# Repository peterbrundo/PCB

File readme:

👋 Hi, I’m @peterbrundo, this is my public github!
👀 I’m interested in printed circuit board design and programing!
🌱 I’m currently learning how to play the accordion!
💞️ I’m looking to collaborate on electrical hardware design
📫 peter.brundage@wayne.edu
👔 linkedin.com/in/peterbrundo
😅 This is a work in progress!

Upcoming projects
➡ PCB Buisness Card USB Keyboard

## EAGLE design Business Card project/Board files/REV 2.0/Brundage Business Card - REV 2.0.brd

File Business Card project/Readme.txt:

TO DO:
Learn how to spell business
Upload code and test
Finish soldering 0201 (0603) capacitors

Project Purpose:

The purpose of the project is to create a buisness card on a printed circuit board with some keyboard functionality! With this project I've had a few key goals in mind

	1) Learn and experiment with USB 2.0 protoco (hardware and software)
	2) Design a PCB to plug directly into a USB port
	3) Develop a working PCB CAD library with associated 3d .stp files
	4) Look and serve as a buisness card (with some style!)
	5) Use 0201 (0603 metric) sized components as a soldering challenge!
	6) Polish up on some documentation skills! (github and this readme for example)

Inspiration:

The main inspiration of this project is definetley this "Stylophone buisness card" project I saw on youtube (https://mitxela.com/projects/stylocard & https://youtu.be/zHVrY_xLM3c). I had been making PCBs at work and at home, and I thought it would be an interesting side project to do in my free time.  I liked the idea because it would be easy to present a buisness card to my friends and family.  To add my own personalized spin, I decided to make it also work as a keyboard. I think there's all sorts of possible applications such as streamdecks, custom macrobased push buttons, numpads, support for non-standard ASCII charecters, or just as a clumsy keyboard alternative. One of my favorite ideas was to have a keyboard to create keybindings for a favorite game of mine, counter strike global offensive.  Each button would correspond to in game items and equipment in the buy menu.  I could even feature some artwork on the pcb to include icons from the game itself as reference. 

V-USB

With a buisness card in mind, I needed to select a microcontroller.  Traditionally I've used Arduino UNO and MEGAs (ATMEGA family) as a starting point but they don't include USB hardware. That's when I found the V-USB library and thought it was a unique way to provide USB functionality to different ATMEGA microncontrollers.  In hindsight, I could also have chosen an Arduino Leonardo or another ATMEGA with hardware usb.  

PCB design:

To make the PCB look like a buisness card, I used a 3.5 x 2.0 inch dimension as a constraint.  I wanted the USB header to fit within these dimensions at the center of the 45 degree bend at the top right corner. 
I wanted the header centered along the curve without exceeding the 3.5 x 2.0 inch dimensions.  First I created a new eagle library and created a USB-A header following the USB 2.0 specification for the required dimenions and pinouts, even including a USB logo as best I could!  With the part in hand, I brushed up my trig to create the 45 degree bend with my USB header centered at the midddle (math included on the "47 Measures layer"). 

I then copied the V-USB circuit schmeatic from the website.  I wanted to give myself a challenge so I included 0201 (0603 Metric) sized capacitors as a soldering challenege!  Those buggers are near impossible to solder with a heat gun, so it's almost a necessiaty to have a microscope on hand.  I did order a stencil and solderpaste for this, but next time I'd rather do it by hand with a soldering iron.  Perhaps i'll include a surface mount version of the ATMEGA8 for more drag soldering practice.

For my personal info, I decided to play around with the different copper and soldermask layers to create some neat effects. The email is incorrect, and I may decide to take the rest of my contact info out from the design files later, but oh well.  

I then created my own eagle components for the rest of the parts from the V-USB schematic and included 3d .step files for everything.  I think there may be a few things that i've used from other libraries, such as the GND and +5V, but it's been a long time!

more info at http://www.obdev.at/vusb/

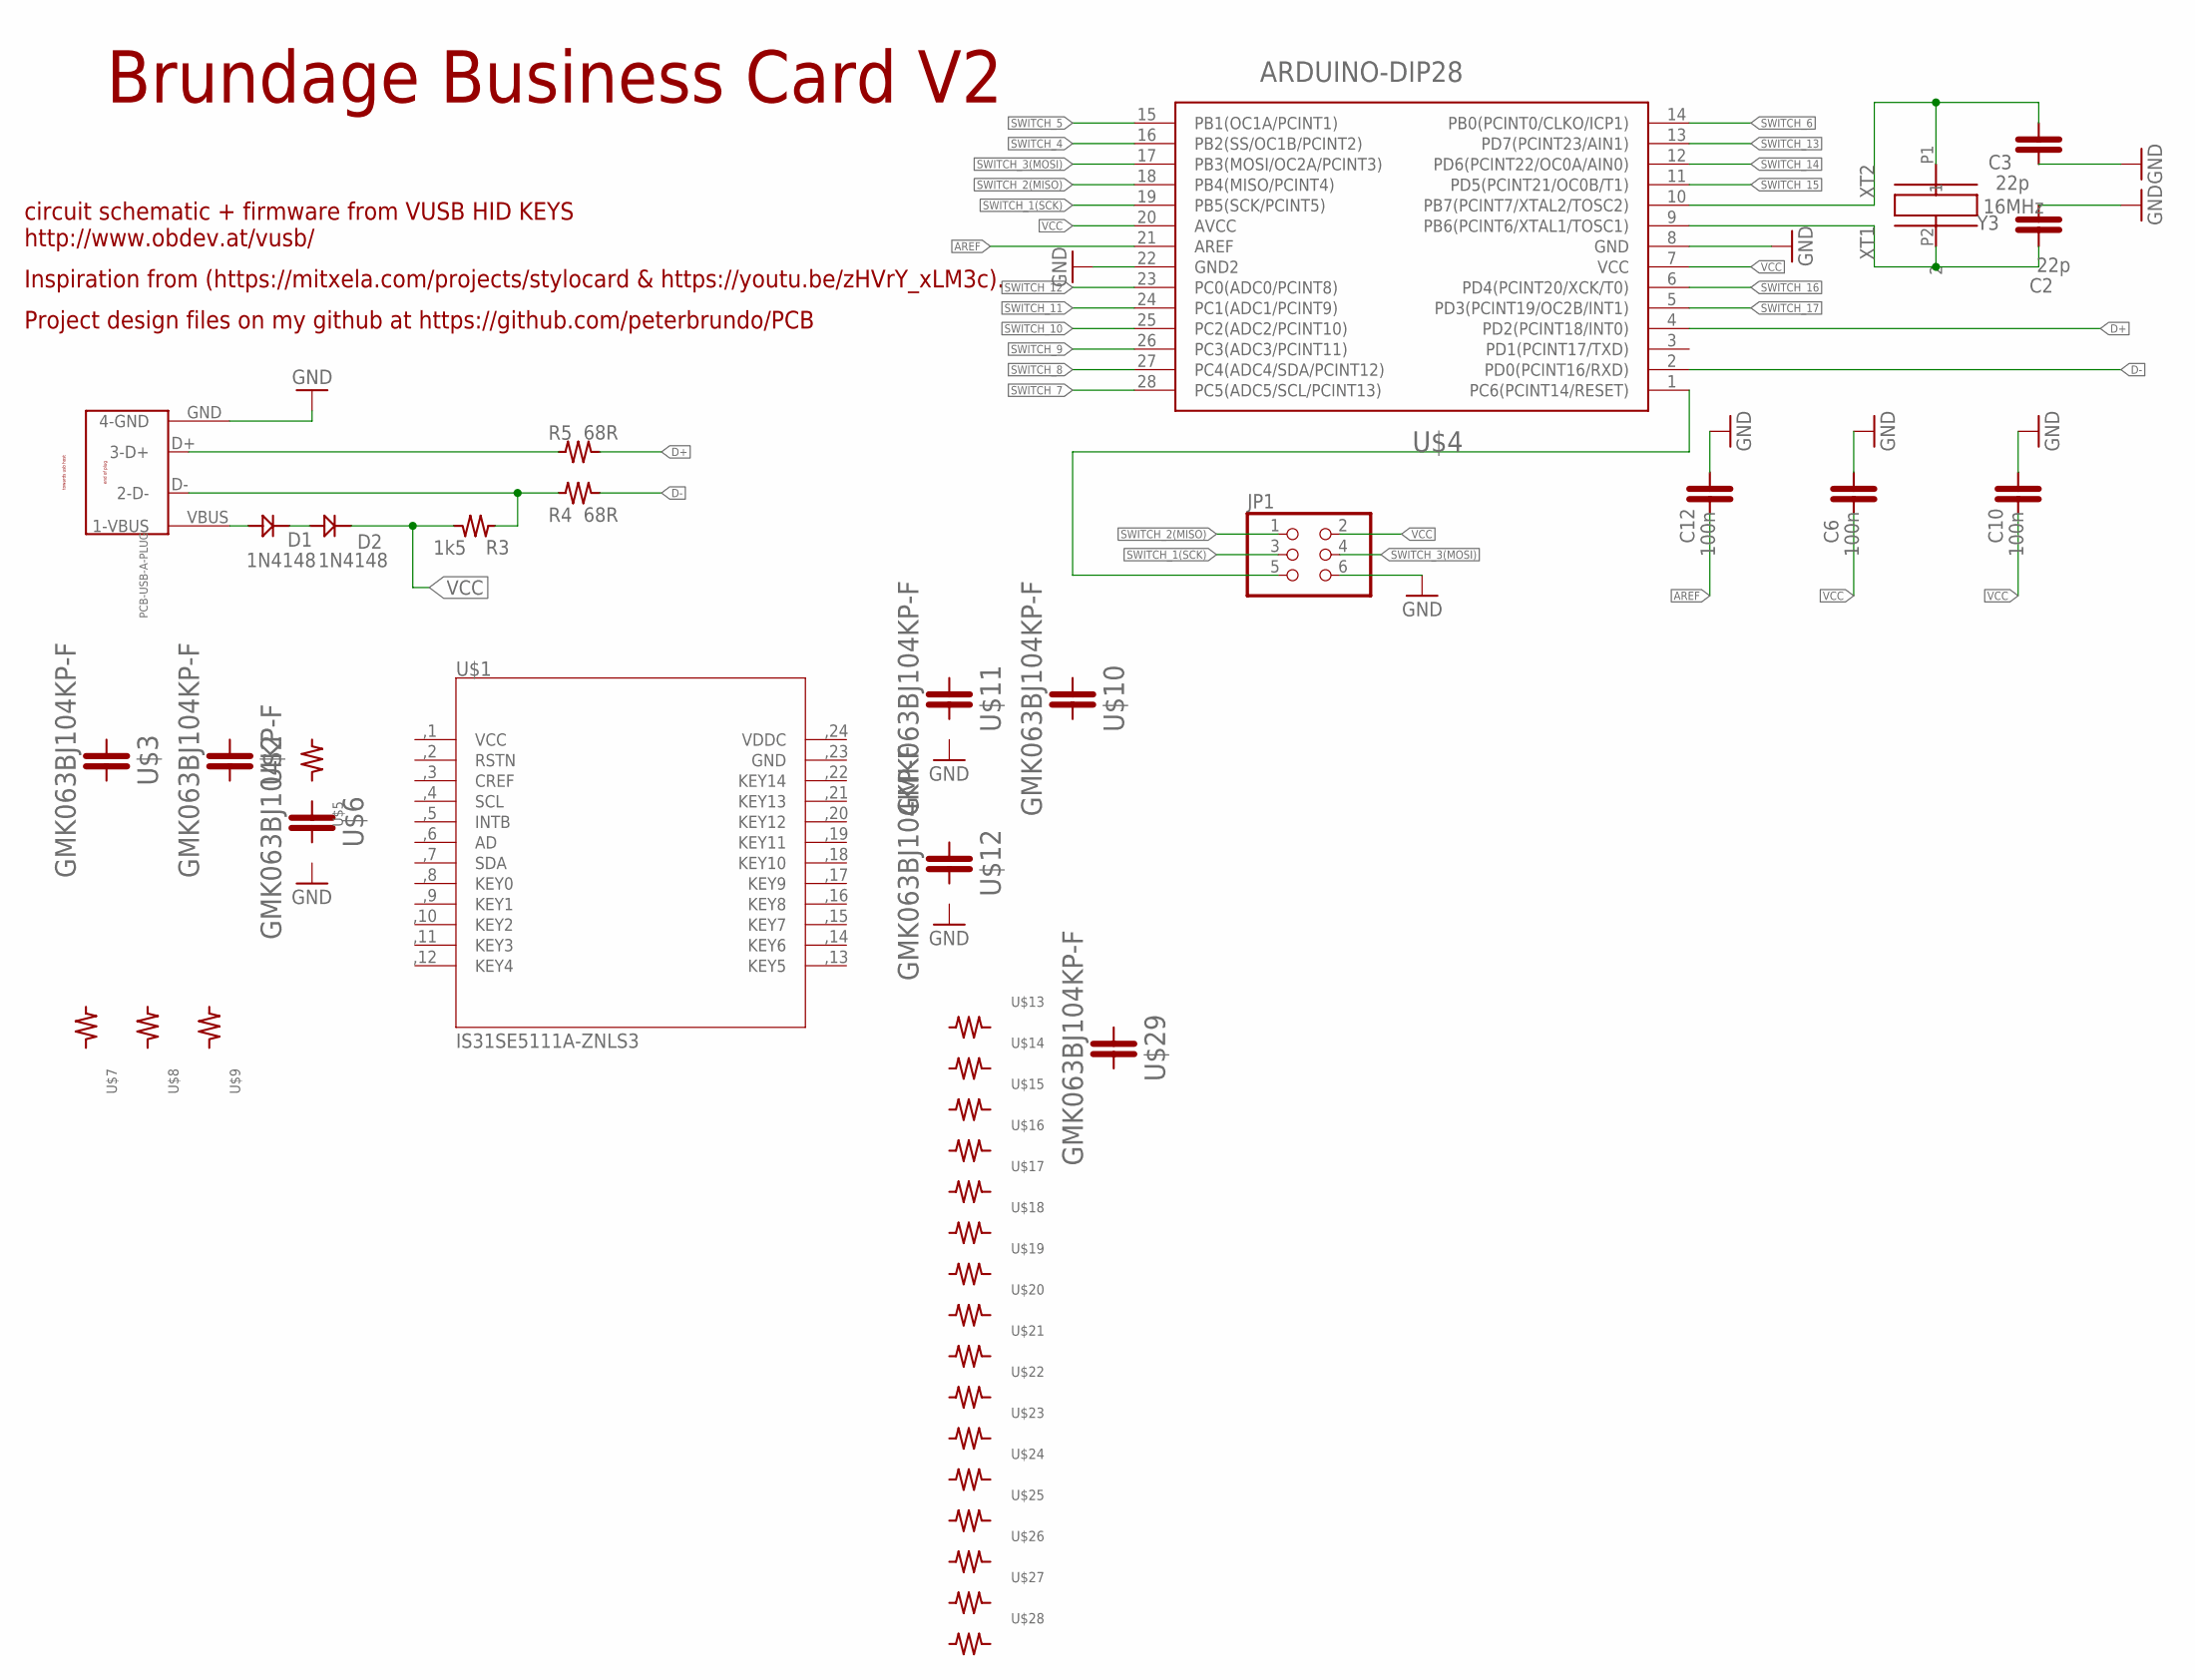
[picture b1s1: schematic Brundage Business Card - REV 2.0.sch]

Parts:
C2, C3: 22p; GRM0225C1E220GA02L
C6, C10, C12: 100n; GMK063BJ104KP-F
D1, D2: 1N4148
JP1: PINHD-2X3; 2X03
PCB-USB-A-PLUG: PCB/USB-SERIES"A"PLUG; USB-SERIES-A-PLUG
R3: 1k5; CRCW06031K50FKEAC
R4, R5: 68R; RCS060368R0FKEA
U$1: IS31SE5111A-ZNLS3; LUMISSIL-TSSOP-24
U$2, U$3, U$6, U$10, U$11, U$12, U$29: GMK063BJ104KP-F
U$4: ARDUINO-DIP28; DIL28-3
U$5, U$7, U$8, U$9, U$13, U$14, U$15, U$16, U$17, U$18, U$19, U$20, U$21, U$22, U$23, U$24, U$25, U$26, U$27, U$28: CRCW06031K50FKEAC
Y3: 16MHz; ABL-8.000MHZ-B2

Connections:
AREF: C12.P2 (2), U$4.21 (AREF)
D+: R5.P2 (2), U$4.4 (PD2(PCINT18/INT0))
D-: R4.P2 (2), U$4.2 (PD0(PCINT16/RXD))
GND: C2.P2 (2), C3.P2 (2), C6.P1 (1), C10.P1 (1), C12.P1 (1), JP1.6, PCB-USB-A-PLUG.GND (4-GND), U$4.8 (GND), U$4.22 (GND2)
unnamed: PCB-USB-A-PLUG.D+ (3-D+), R5.P1 (1)
unnamed: PCB-USB-A-PLUG.D- (2-D-), R3.P1 (1), R4.P1 (1)
unnamed: D1.ANODE(+), PCB-USB-A-PLUG.VBUS (1-VBUS)
unnamed: D1.CATHODE(-), D2.ANODE(+)
unnamed: JP1.5, U$4.1 (PC6(PCINT14/RESET))
SWITCH_1(SCK): JP1.3, U$4.19 (PB5(SCK/PCINT5))
SWITCH_2(MISO): JP1.1, U$4.18 (PB4(MISO/PCINT4))
SWITCH_3(MOSI): JP1.4, U$4.17 (PB3(MOSI/OC2A/PCINT3))
SWITCH_4: U$4.16 (PB2(SS/OC1B/PCINT2))
SWITCH_5: U$4.15 (PB1(OC1A/PCINT1))
SWITCH_6: U$4.14 (PB0(PCINT0/CLKO/ICP1))
SWITCH_7: U$4.28 (PC5(ADC5/SCL/PCINT13))
SWITCH_8: U$4.27 (PC4(ADC4/SDA/PCINT12))
SWITCH_9: U$4.26 (PC3(ADC3/PCINT11))
SWITCH_10: U$4.25 (PC2(ADC2/PCINT10))
SWITCH_11: U$4.24 (PC1(ADC1/PCINT9))
SWITCH_12: U$4.23 (PC0(ADC0/PCINT8))
SWITCH_13: U$4.13 (PD7(PCINT23/AIN1))
SWITCH_14: U$4.12 (PD6(PCINT22/OC0A/AIN0))
SWITCH_15: U$4.11 (PD5(PCINT21/OC0B/T1))
SWITCH_16: U$4.6 (PD4(PCINT20/XCK/T0))
SWITCH_17: U$4.5 (PD3(PCINT19/OC2B/INT1))
VCC: C6.P2 (2), C10.P2 (2), D2.CATHODE(-), JP1.2, R3.P2 (2), U$4.7 (VCC), U$4.20 (AVCC)
XT1: C2.P1 (1), U$4.9 (PB6(PCINT6/XTAL1/TOSC1)), Y3.P2 (2)
XT2: C3.P1 (1), U$4.10 (PB7(PCINT7/XTAL2/TOSC2)), Y3.P1 (1)

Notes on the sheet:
Brundage Business Card V2
circuit schematic + firmware from VUSB HID KEYS http://www.obdev.at/vusb/
Project design files on my github at https://github.com/peterbrundo/PCB
Inspiration from (https://mitxela.com/projects/stylocard & https://youtu.be/zHVrY_xLM3c).

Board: 2 copper layers, 42 parts (0 on the bottom side), 15 nets, no tracks yet.

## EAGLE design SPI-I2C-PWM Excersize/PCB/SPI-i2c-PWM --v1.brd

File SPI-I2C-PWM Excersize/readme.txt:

#"SPI-I2C-PWM EXCERCISE"
	
##Initial Goals: 
	Development board for SPI-I2C protocols using multiple MCUs
	SMD soldering practice (SOIC and 0805,0603)
	R2R ladder approach for analog dipswitches
	Test out SPI/i2c protocols, PWM clock generation
	PDIP packages with thru hole sockets -swapable parts
	
##Basic Concept:
	Parent MCU send 8 bit messages to child MCUs
	User configruable paramters 
		communication protocol-SPI-i2c-PWM
		child rx
		8bit message 
		Additional features 
			10bit adc potentiometer
			additional commands - tx/rx
	8bit led shift regsiter displays (parent and child bit bang)
	Additional features selected by 10bit R2r ladder
##Resources: 
	Arudino i2c library 
	myshift register bit banging library

##Reach Goals: 
	Develop custom firmware to support I2C handles (somewhat out of scope)
	i2c bus arbitration (message priority)
	SPI child / parent swap
	Add UART(? - annoying reworks or new board)
	
##Thoughts/reflections:
	-Should've included pinouts for UART communication
	-Pinouts for a USB COM port, JTAG or ICSP (duh!)
	-Reworks are to make it work! Not to make it pretty!

*readme update 11-29-2021*

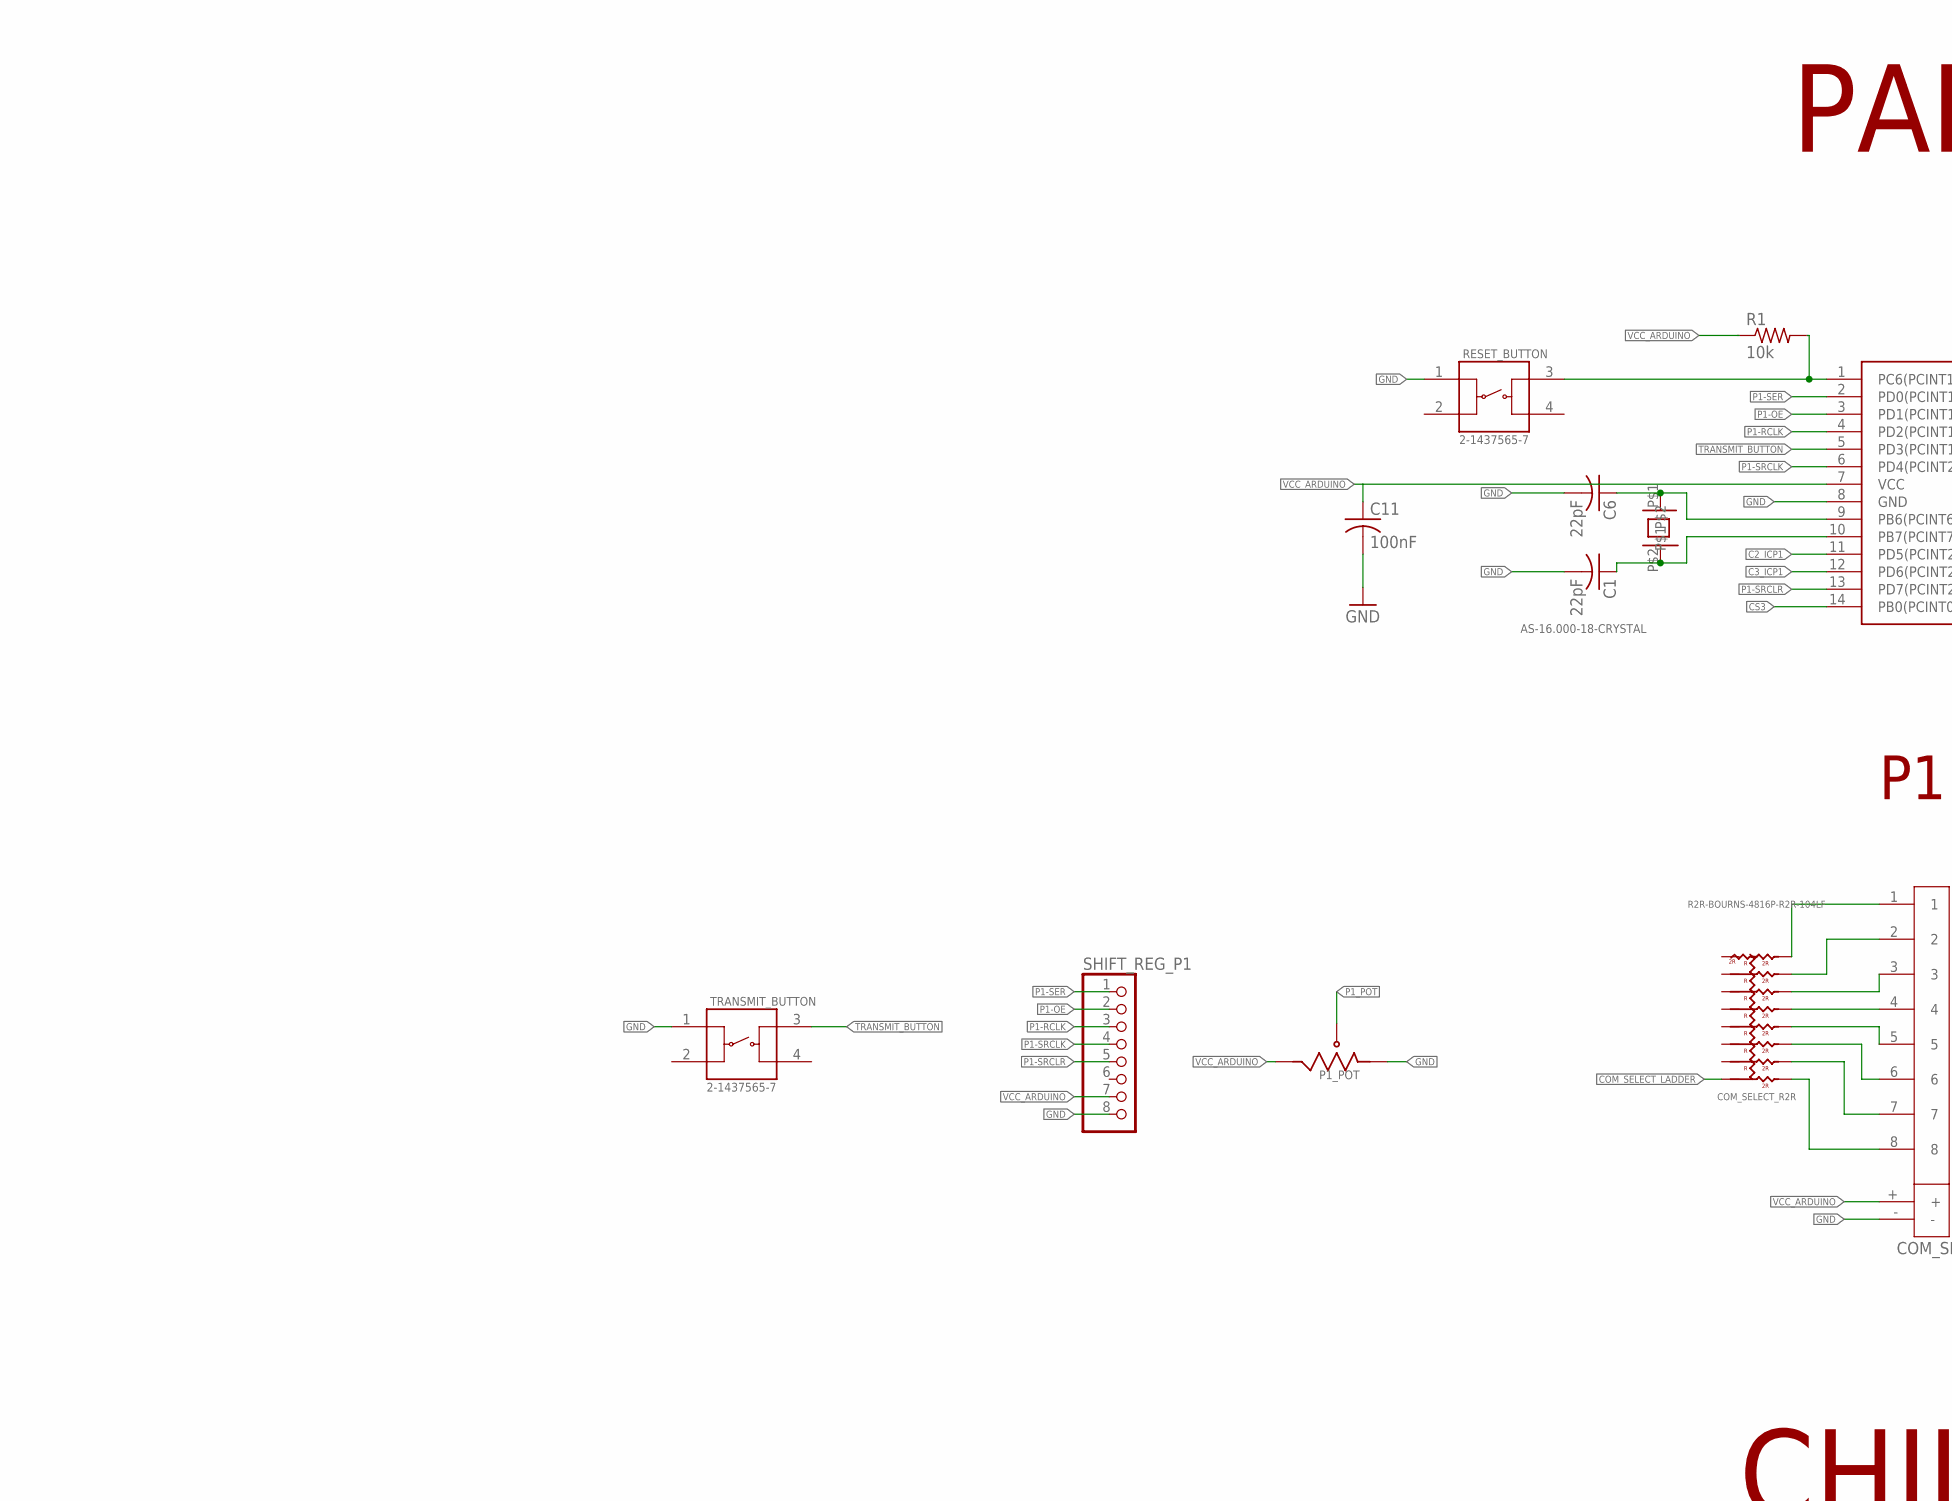
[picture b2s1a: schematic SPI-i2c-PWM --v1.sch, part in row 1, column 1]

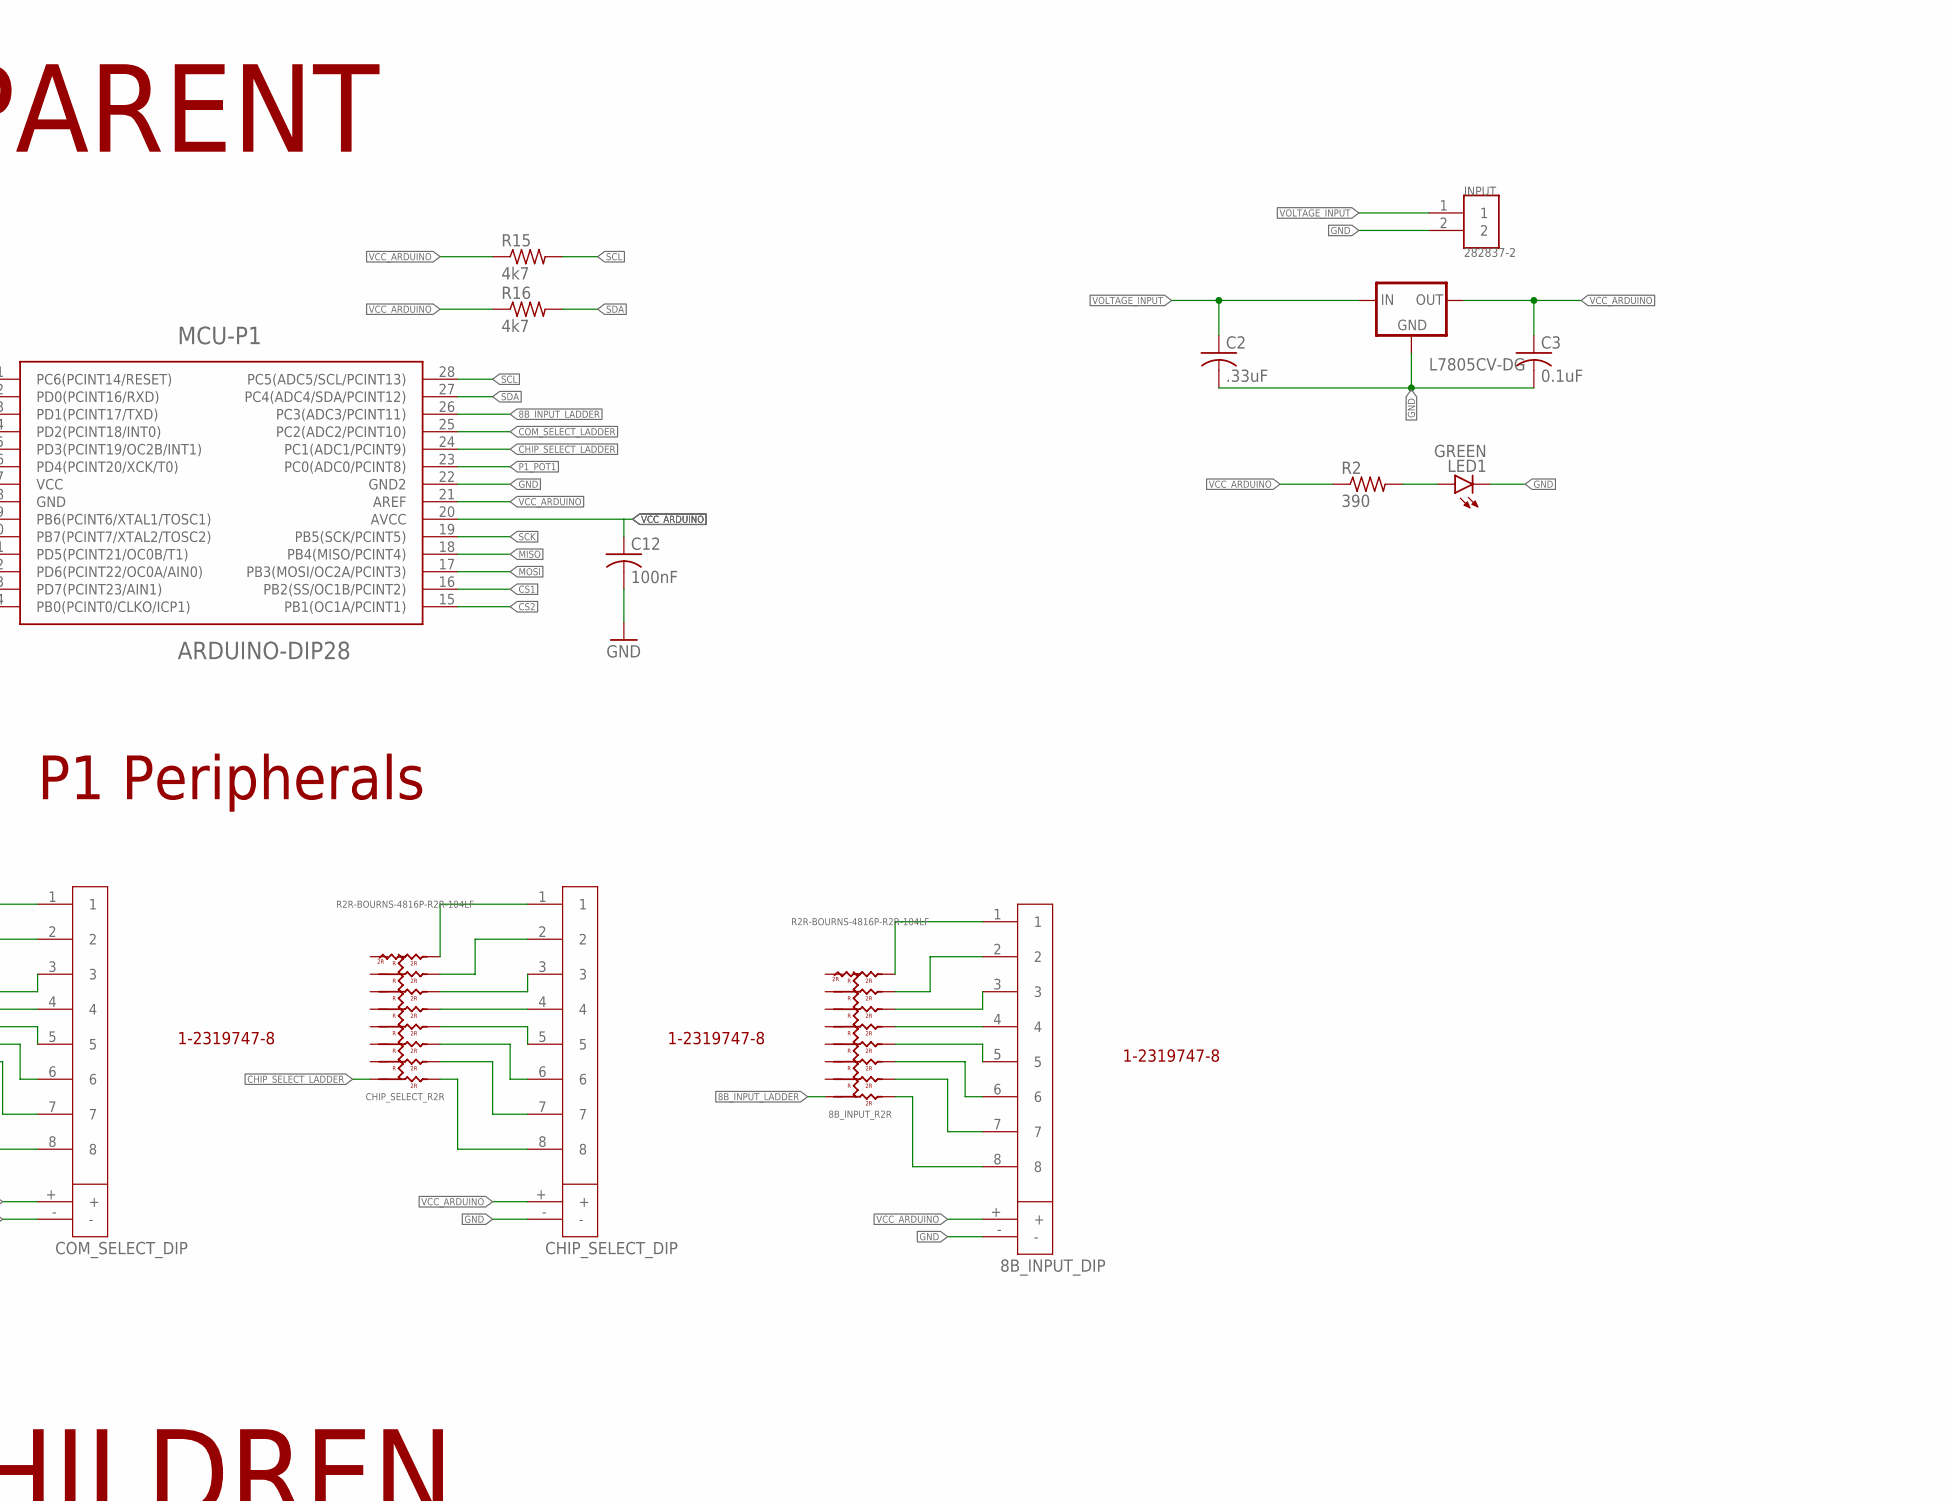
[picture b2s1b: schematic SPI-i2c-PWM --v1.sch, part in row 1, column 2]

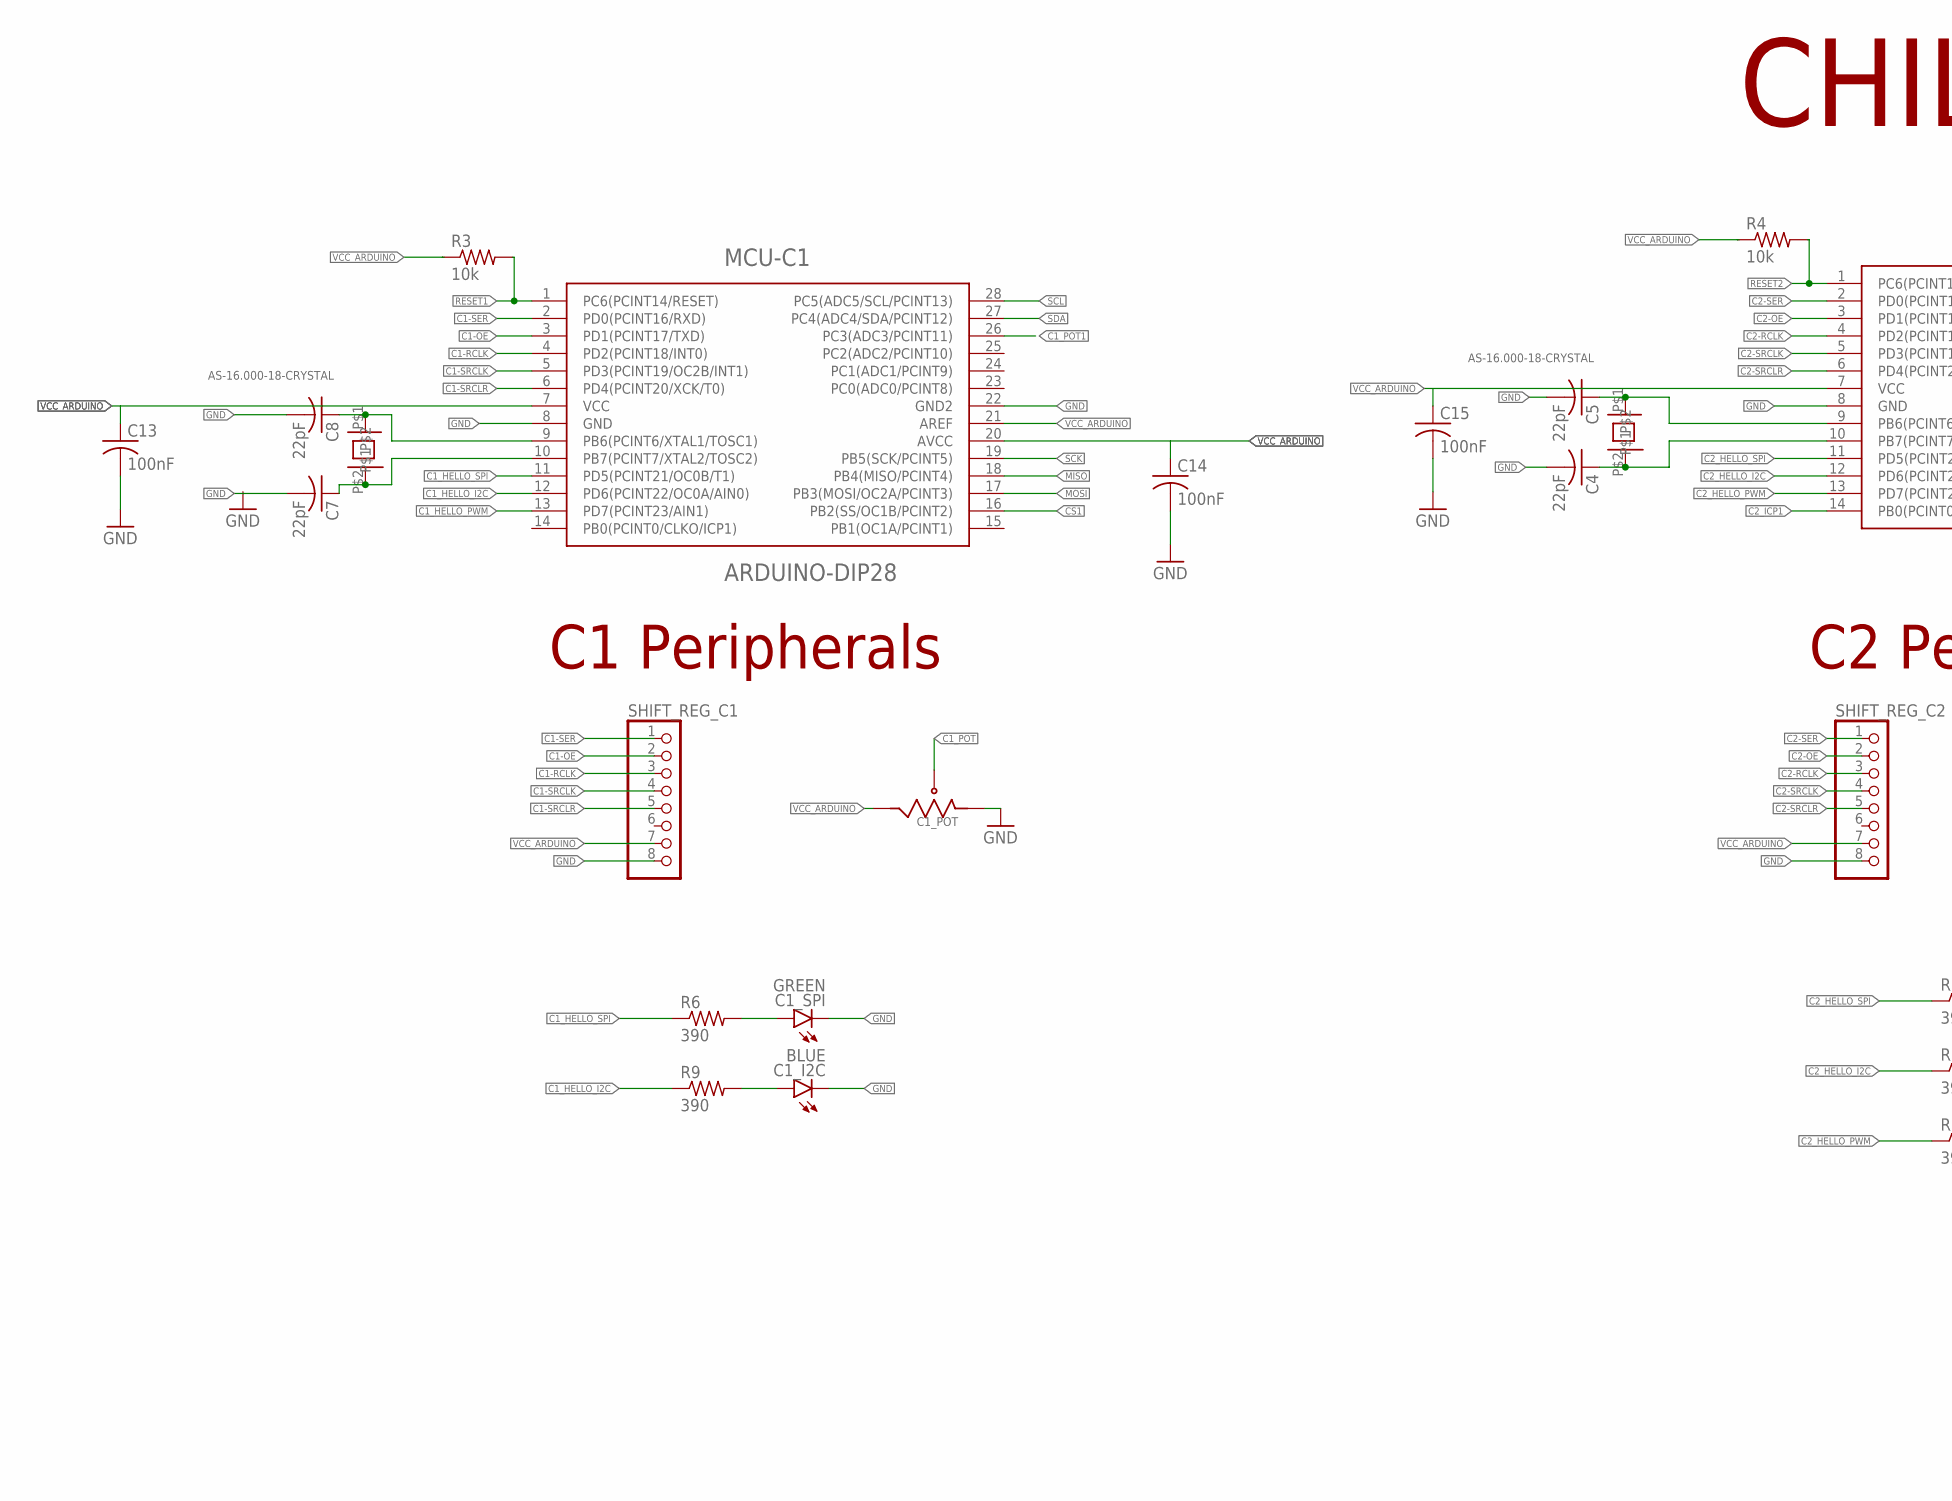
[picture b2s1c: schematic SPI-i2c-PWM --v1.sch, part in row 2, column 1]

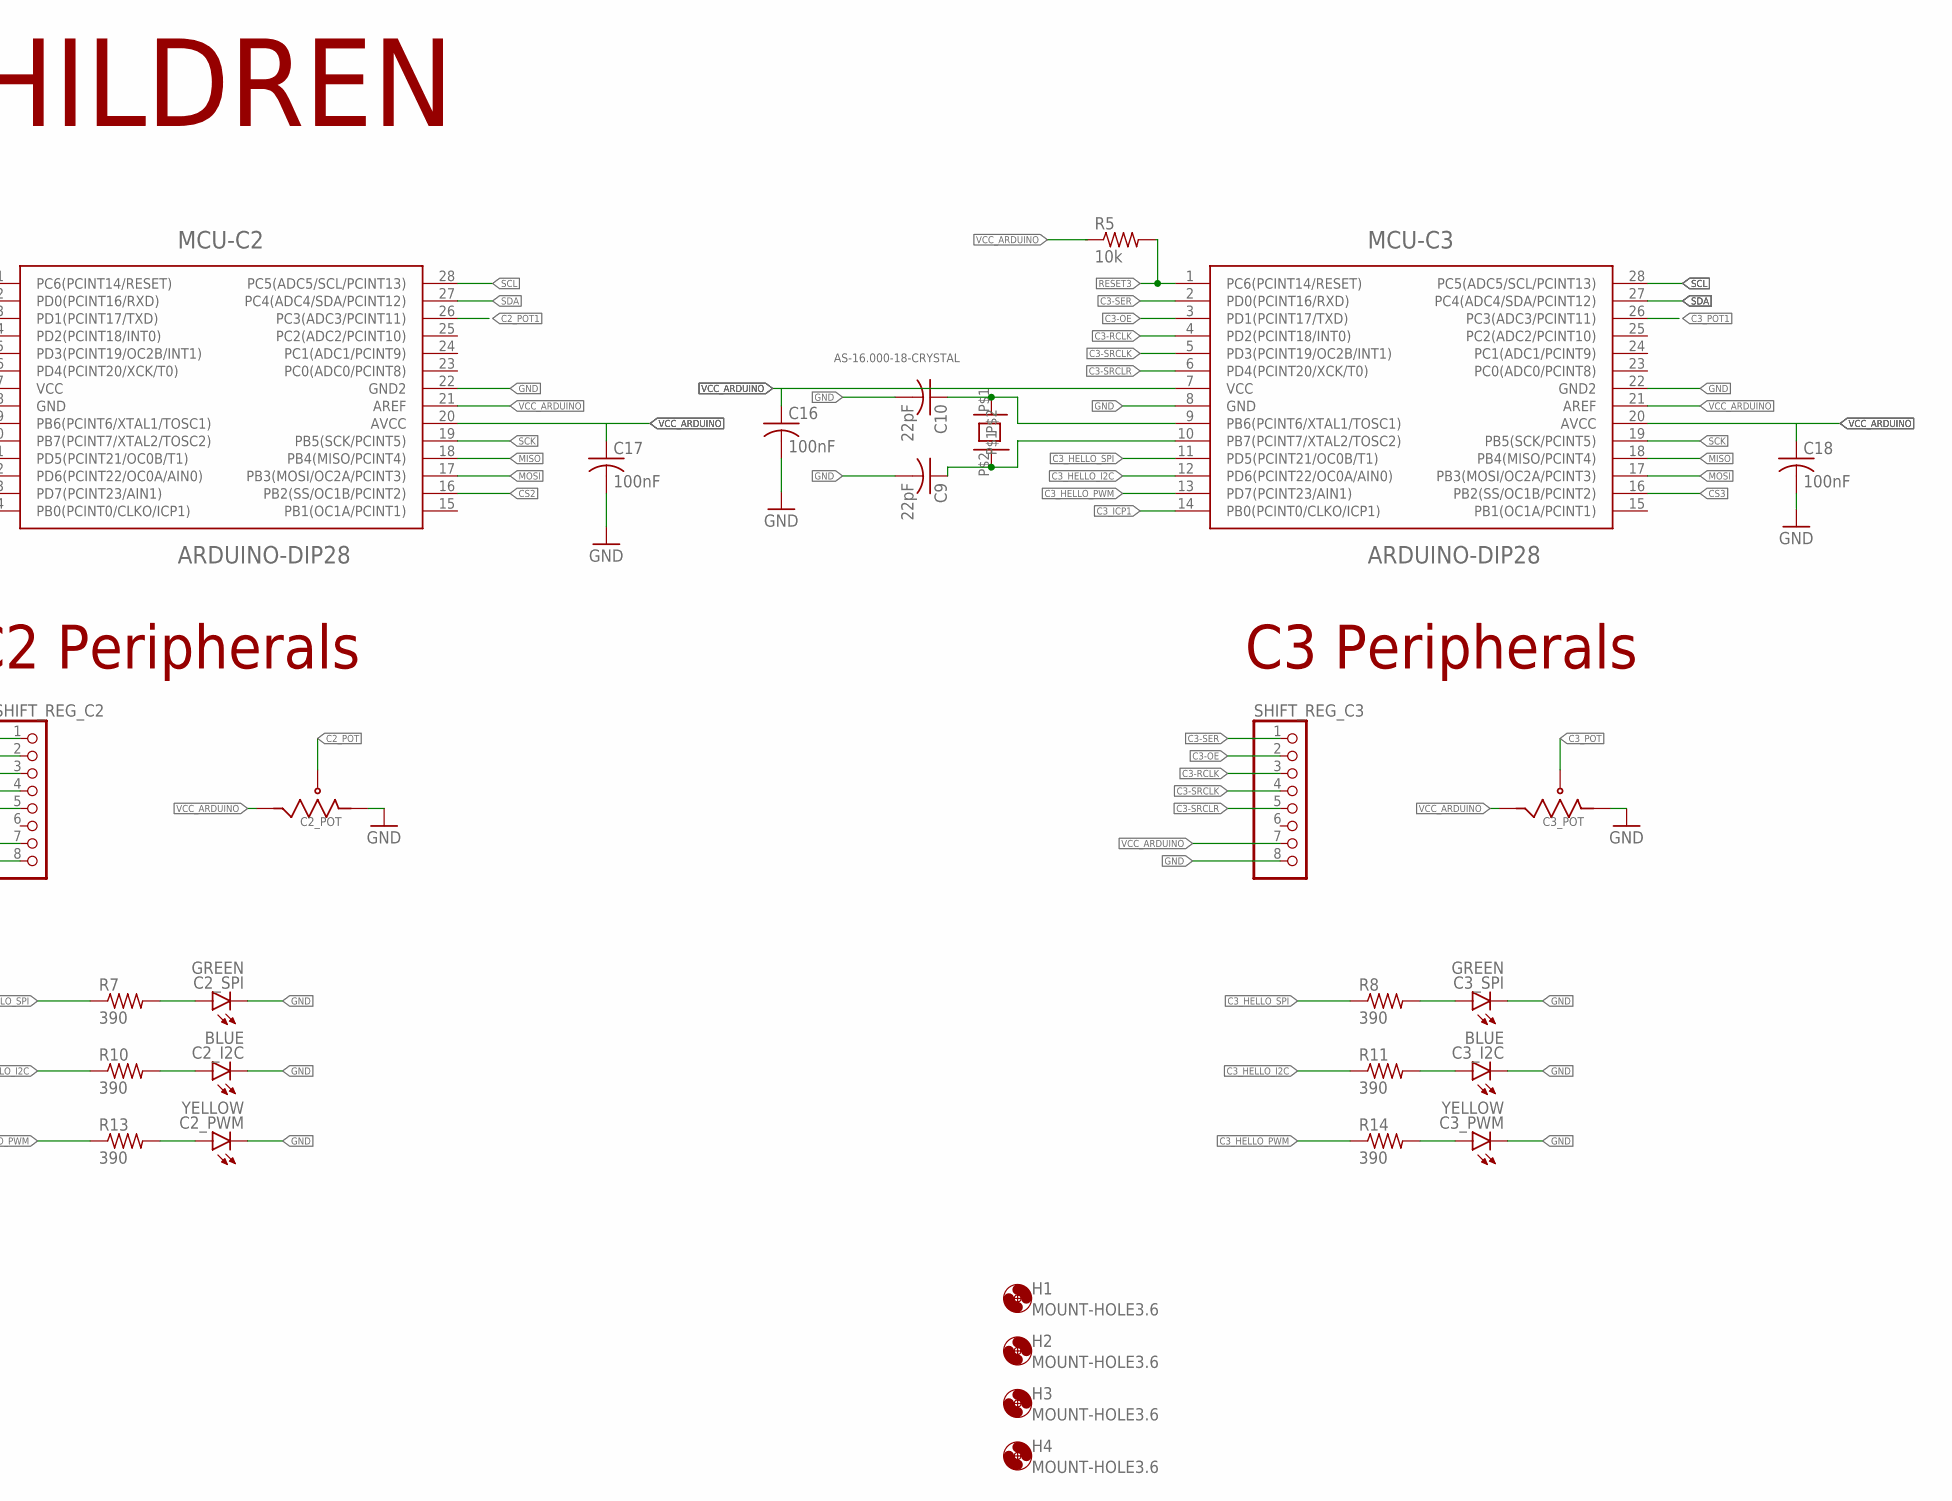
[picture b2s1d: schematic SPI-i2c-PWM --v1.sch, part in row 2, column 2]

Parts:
5V_REG: L7805CV-DG; 78XXS
8B_INPUT_DIP: DIP8-TE; DIP8-TE(1-2319747-8)
8B_INPUT_R2R: R2R-BOURNS-4816P-R2R-104LF; R2RLADDER
C1, C4, C5, C6, C7, C8, C9, C10: 22pF; C0805
C1_I2C, C2_I2C, C3_I2C: BLUE; CHIP-LED0805
C1_POT, C2_POT, C3_POT: POTENTIOMETER-ALLIE; POT-ALLIEEXPRESS
C1_SPI, C2_SPI, C3_SPI: GREEN; CHIP-LED0805
C2: .33uF; C0805
C2_PWM, C3_PWM: YELLOW; CHIP-LED0805
C3: 0.1uF; C0805
C11, C12, C13, C14, C15, C16, C17, C18: 100nF; C0805
CHIP_SELECT_DIP: DIP8-TE; DIP8-TE(1-2319747-8)
CHIP_SELECT_R2R: R2R-BOURNS-4816P-R2R-104LF; R2RLADDER
COM_SELECT_DIP: DIP8-TE; DIP8-TE(1-2319747-8)
COM_SELECT_R2R: R2R-BOURNS-4816P-R2R-104LF; R2RLADDER
H1, H2, H3, H4: MOUNT-HOLE3.6; 3,6
INPUT: 282837-2; TE_282837-2
LED1: GREEN; CHIPLED_0805
M1_OSC: AS-16.000-18-CRYSTAL
MCU-C1, MCU-C2, MCU-C3: ARDUINO-DIP28; DIL28-3
MCU-P1: ARDUINO-DIP28; DIL28-3
P1_POT: POTENTIOMETER-ALLIE; POT-ALLIEEXPRESS
R1, R3, R4, R5: 10k; M0805
R2: 390; R0805
R6, R7, R8, R9, R10, R11, R13, R14: 390; M0805
R15, R16: 4k7; R0805
RESET_BUTTON: 2-1437565-7; SW_2-1437565-7
S1_OSC, S2_OSC, S3_OSC: AS-16.000-18-CRYSTAL
SHIFT_REG_C1, SHIFT_REG_C2, SHIFT_REG_C3: PINHD-1X8; 1X08
SHIFT_REG_P1: PINHD-1X8; 1X08
TRANSMIT_BUTTON: 2-1437565-7; SW_2-1437565-7

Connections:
8B_INPUT_LADDER: 8B_INPUT_R2R.16, MCU-P1.26 (PC3(ADC3/PCINT11))
C1-OE: MCU-C1.3 (PD1(PCINT17/TXD)), SHIFT_REG_C1.2
C1-RCLK: MCU-C1.4 (PD2(PCINT18/INT0)), SHIFT_REG_C1.3
C1-SER: MCU-C1.2 (PD0(PCINT16/RXD)), SHIFT_REG_C1.1
C1-SRCLK: MCU-C1.5 (PD3(PCINT19/OC2B/INT1)), SHIFT_REG_C1.4
C1-SRCLR: MCU-C1.6 (PD4(PCINT20/XCK/T0)), SHIFT_REG_C1.5
C1_HELLO_I2C: MCU-C1.12 (PD6(PCINT22/OC0A/AIN0)), R9.1
C1_HELLO_PWM: MCU-C1.13 (PD7(PCINT23/AIN1))
C1_HELLO_SPI: MCU-C1.11 (PD5(PCINT21/OC0B/T1)), R6.1
C1_POT: C1_POT.P$2
C1_POT1: MCU-C1.26 (PC3(ADC3/PCINT11))
C2-OE: MCU-C2.3 (PD1(PCINT17/TXD)), SHIFT_REG_C2.2
C2-RCLK: MCU-C2.4 (PD2(PCINT18/INT0)), SHIFT_REG_C2.3
C2-SER: MCU-C2.2 (PD0(PCINT16/RXD)), SHIFT_REG_C2.1
C2-SRCLK: MCU-C2.5 (PD3(PCINT19/OC2B/INT1)), SHIFT_REG_C2.4
C2-SRCLR: MCU-C2.6 (PD4(PCINT20/XCK/T0)), SHIFT_REG_C2.5
C2_HELLO_I2C: MCU-C2.12 (PD6(PCINT22/OC0A/AIN0)), R10.1
C2_HELLO_PWM: MCU-C2.13 (PD7(PCINT23/AIN1)), R13.1
C2_HELLO_SPI: MCU-C2.11 (PD5(PCINT21/OC0B/T1)), R7.1
C2_ICP1: MCU-C2.14 (PB0(PCINT0/CLKO/ICP1)), MCU-P1.11 (PD5(PCINT21/OC0B/T1))
C2_POT: C2_POT.P$2
C2_POT1: MCU-C2.26 (PC3(ADC3/PCINT11))
C3-OE: MCU-C3.3 (PD1(PCINT17/TXD)), SHIFT_REG_C3.2
C3-RCLK: MCU-C3.4 (PD2(PCINT18/INT0)), SHIFT_REG_C3.3
C3-SER: MCU-C3.2 (PD0(PCINT16/RXD)), SHIFT_REG_C3.1
C3-SRCLK: MCU-C3.5 (PD3(PCINT19/OC2B/INT1)), SHIFT_REG_C3.4
C3-SRCLR: MCU-C3.6 (PD4(PCINT20/XCK/T0)), SHIFT_REG_C3.5
C3_HELLO_I2C: MCU-C3.12 (PD6(PCINT22/OC0A/AIN0)), R11.1
C3_HELLO_PWM: MCU-C3.13 (PD7(PCINT23/AIN1)), R14.1
C3_HELLO_SPI: MCU-C3.11 (PD5(PCINT21/OC0B/T1)), R8.1
C3_ICP1: MCU-C3.14 (PB0(PCINT0/CLKO/ICP1)), MCU-P1.12 (PD6(PCINT22/OC0A/AIN0))
C3_POT: C3_POT.P$2
C3_POT1: MCU-C3.26 (PC3(ADC3/PCINT11))
CHIP_SELECT_LADDER: CHIP_SELECT_R2R.16, MCU-P1.24 (PC1(ADC1/PCINT9))
COM_SELECT_LADDER: COM_SELECT_R2R.16, MCU-P1.25 (PC2(ADC2/PCINT10))
CS1: MCU-C1.16 (PB2(SS/OC1B/PCINT2)), MCU-P1.16 (PB2(SS/OC1B/PCINT2))
CS2: MCU-C2.16 (PB2(SS/OC1B/PCINT2)), MCU-P1.15 (PB1(OC1A/PCINT1))
CS3: MCU-C3.16 (PB2(SS/OC1B/PCINT2)), MCU-P1.14 (PB0(PCINT0/CLKO/ICP1))
GND: 5V_REG.GND, 8B_INPUT_DIP.-, C1.2, C1_I2C.C, C1_POT.P$3, C1_SPI.C, C2.2, C2_I2C.C, C2_POT.P$3, C2_PWM.C, C2_SPI.C, C3.2, C3_I2C.C, C3_POT.P$3, C3_PWM.C, C3_SPI.C, C4.2, C5.2, C6.2, C7.2, C8.2, C9.2, C10.2, C11.2, C12.2, C13.2, C14.2, C15.2, C16.2, C17.2, C18.2, CHIP_SELECT_DIP.-, COM_SELECT_DIP.-, INPUT.2, LED1.C, MCU-C1.8 (GND), MCU-C1.22 (GND2), MCU-C2.8 (GND), MCU-C2.22 (GND2), MCU-C3.8 (GND), MCU-C3.22 (GND2), MCU-P1.8 (GND), MCU-P1.22 (GND2), P1_POT.P$3, RESET_BUTTON.1, SHIFT_REG_C1.8, SHIFT_REG_C2.8, SHIFT_REG_C3.8, SHIFT_REG_P1.8, TRANSMIT_BUTTON.1
MISO: MCU-C1.18 (PB4(MISO/PCINT4)), MCU-C2.18 (PB4(MISO/PCINT4)), MCU-C3.18 (PB4(MISO/PCINT4)), MCU-P1.18 (PB4(MISO/PCINT4))
MOSI: MCU-C1.17 (PB3(MOSI/OC2A/PCINT3)), MCU-C2.17 (PB3(MOSI/OC2A/PCINT3)), MCU-C3.17 (PB3(MOSI/OC2A/PCINT3)), MCU-P1.17 (PB3(MOSI/OC2A/PCINT3))
unnamed: LED1.A, R2.2
unnamed: C8.1, MCU-C1.9 (PB6(PCINT6/XTAL1/TOSC1)), S1_OSC.P$1
unnamed: C7.1, MCU-C1.10 (PB7(PCINT7/XTAL2/TOSC2)), S1_OSC.P$2
unnamed: 8B_INPUT_DIP.1, 8B_INPUT_R2R.8
unnamed: C6.1, M1_OSC.P$1, MCU-P1.9 (PB6(PCINT6/XTAL1/TOSC1))
unnamed: C1.1, M1_OSC.P$2, MCU-P1.10 (PB7(PCINT7/XTAL2/TOSC2))
unnamed: C5.1, MCU-C2.9 (PB6(PCINT6/XTAL1/TOSC1)), S2_OSC.P$1
unnamed: C4.1, MCU-C2.10 (PB7(PCINT7/XTAL2/TOSC2)), S2_OSC.P$2
unnamed: C10.1, MCU-C3.9 (PB6(PCINT6/XTAL1/TOSC1)), S3_OSC.P$1
unnamed: C9.1, MCU-C3.10 (PB7(PCINT7/XTAL2/TOSC2)), S3_OSC.P$2
unnamed: 8B_INPUT_DIP.2, 8B_INPUT_R2R.7
unnamed: C1_SPI.A, R6.2
unnamed: C2_SPI.A, R7.2
unnamed: C3_SPI.A, R8.2
unnamed: C1_I2C.A, R9.2
unnamed: C2_I2C.A, R10.2
unnamed: C3_I2C.A, R11.2
unnamed: COM_SELECT_DIP.1, COM_SELECT_R2R.8
unnamed: C2_PWM.A, R13.2
unnamed: C3_PWM.A, R14.2
unnamed: 8B_INPUT_DIP.3, 8B_INPUT_R2R.6
unnamed: 8B_INPUT_DIP.4, 8B_INPUT_R2R.5
unnamed: 8B_INPUT_DIP.5, 8B_INPUT_R2R.4
unnamed: 8B_INPUT_DIP.6, 8B_INPUT_R2R.3
unnamed: 8B_INPUT_DIP.7, 8B_INPUT_R2R.2
unnamed: 8B_INPUT_DIP.8, 8B_INPUT_R2R.1
unnamed: COM_SELECT_DIP.2, COM_SELECT_R2R.7
unnamed: COM_SELECT_DIP.3, COM_SELECT_R2R.6
unnamed: COM_SELECT_DIP.4, COM_SELECT_R2R.5
unnamed: COM_SELECT_DIP.5, COM_SELECT_R2R.4
unnamed: COM_SELECT_DIP.6, COM_SELECT_R2R.3
unnamed: COM_SELECT_DIP.7, COM_SELECT_R2R.2
unnamed: COM_SELECT_DIP.8, COM_SELECT_R2R.1
unnamed: CHIP_SELECT_DIP.1, CHIP_SELECT_R2R.8
unnamed: CHIP_SELECT_DIP.2, CHIP_SELECT_R2R.7
unnamed: CHIP_SELECT_DIP.3, CHIP_SELECT_R2R.6
unnamed: CHIP_SELECT_DIP.4, CHIP_SELECT_R2R.5
unnamed: CHIP_SELECT_DIP.5, CHIP_SELECT_R2R.4
unnamed: CHIP_SELECT_DIP.6, CHIP_SELECT_R2R.3
unnamed: CHIP_SELECT_DIP.7, CHIP_SELECT_R2R.2
unnamed: CHIP_SELECT_DIP.8, CHIP_SELECT_R2R.1
P1-OE: MCU-P1.3 (PD1(PCINT17/TXD)), SHIFT_REG_P1.2
P1-RCLK: MCU-P1.4 (PD2(PCINT18/INT0)), SHIFT_REG_P1.3
P1-SER: MCU-P1.2 (PD0(PCINT16/RXD)), SHIFT_REG_P1.1
P1-SRCLK: MCU-P1.6 (PD4(PCINT20/XCK/T0)), SHIFT_REG_P1.4
P1-SRCLR: MCU-P1.13 (PD7(PCINT23/AIN1)), SHIFT_REG_P1.5
P1_POT: P1_POT.P$2
P1_POT1: MCU-P1.23 (PC0(ADC0/PCINT8))
RESET1: MCU-C1.1 (PC6(PCINT14/RESET)), R3.2
RESET2: MCU-C2.1 (PC6(PCINT14/RESET)), R4.2
RESET3: MCU-C3.1 (PC6(PCINT14/RESET)), R5.2
RESET_BUTTON: MCU-P1.1 (PC6(PCINT14/RESET)), R1.2, RESET_BUTTON.3
SCK: MCU-C1.19 (PB5(SCK/PCINT5)), MCU-C2.19 (PB5(SCK/PCINT5)), MCU-C3.19 (PB5(SCK/PCINT5)), MCU-P1.19 (PB5(SCK/PCINT5))
SCL: MCU-C1.28 (PC5(ADC5/SCL/PCINT13)), MCU-C2.28 (PC5(ADC5/SCL/PCINT13)), MCU-C3.28 (PC5(ADC5/SCL/PCINT13)), MCU-P1.28 (PC5(ADC5/SCL/PCINT13)), R15.2
SDA: MCU-C1.27 (PC4(ADC4/SDA/PCINT12)), MCU-C2.27 (PC4(ADC4/SDA/PCINT12)), MCU-C3.27 (PC4(ADC4/SDA/PCINT12)), MCU-P1.27 (PC4(ADC4/SDA/PCINT12)), R16.2
TRANSMIT_BUTTON: MCU-P1.5 (PD3(PCINT19/OC2B/INT1)), TRANSMIT_BUTTON.3
VCC_ARDUINO: 5V_REG.OUT, 8B_INPUT_DIP.+, C1_POT.P$1, C2_POT.P$1, C3.1, C3_POT.P$1, C11.1, C12.1, C13.1, C14.1, C15.1, C16.1, C17.1, C18.1, CHIP_SELECT_DIP.+, COM_SELECT_DIP.+, MCU-C1.7 (VCC), MCU-C1.20 (AVCC), MCU-C1.21 (AREF), MCU-C2.7 (VCC), MCU-C2.20 (AVCC), MCU-C2.21 (AREF), MCU-C3.7 (VCC), MCU-C3.20 (AVCC), MCU-C3.21 (AREF), MCU-P1.7 (VCC), MCU-P1.20 (AVCC), MCU-P1.21 (AREF), P1_POT.P$1, R1.1, R2.1, R3.1, R4.1, R5.1, R15.1, R16.1, SHIFT_REG_C1.7, SHIFT_REG_C2.7, SHIFT_REG_C3.7, SHIFT_REG_P1.7
VOLTAGE_INPUT: 5V_REG.IN, C2.1, INPUT.1

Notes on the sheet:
CHILDREN
C1 Peripherals
PARENT
C2 Peripherals
C3 Peripherals
P1 Peripherals

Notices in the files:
parts and their libraries:
SparkFun: Licensing: CC v3.0 Share-Alike You are welcome to use this library for commercial purposes.
